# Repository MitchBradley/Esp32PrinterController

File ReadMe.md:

# ESP32 3D Printer Controller

This is based on https://github.com/felixstorm/Creality_Ender_3_ESP32_Board.git with the following changes

- Laid out for 2-sided PCB fabrication instead of PCB routing.  2-sided PCBs are available at very low cost from various prototyping shops, and provide much better grounding and power distribution.
- Can use either Pololu stepper driver modules or external drivers, selected by solder jumpers.
- The microstepping ratio can be selected by solder jumpers, or those pins can be connected to SPI for fine-grained configuration of TMC modules.  The X Y and Z axes all use the same microstepping/SPI settings, whereas the extruder can be configured independently of X, Y, Z.
- The I/O voltage to the shift registers and stepper modules can be either 3V3 or 5V, selected by solder jumper.  3V3 is appropriate for TMC modules where the SPI output goes back to the ESP32.  5V is best for external drivers whose optocoupler inputs work best at 5V.  Non-TMC stepper modules can use either.
- The micro SD card socket uses a Wemos D1 Mini shield which has a smaller footprint than the one on the original design, permitting all the drivers to be placed along one edge of the board.
- The connectors along the bottom edge of the board, and the power input connector, are all pluggable terminal blocks, thus permitting easy disconnection of the signals for assembly and maintenance.  The layout permits each signal pair to be on its own plug, or everything on one longer plug, or any combination thereof, at the users discretion.
- For the steppers, you can choose either 0.1" pitch connectors - e.g. pin headers with Dupont connectors - or 0.15" pitch pluggable terminal blocks (or 0.15" screw terminals, but pluggable is easier to wire and maintain).
- The fuse holders were spread out to make it easier to get your fingers in to grab the fuses.

The design passes acceptance checks for the aisler.net entry level prototyping service.

Update: The board is fully functional.  If you would like to build it, contact me and I will upload the revised version that fixes a few silkscreen errors and provides better clearance between some components that were a little crowded.

*Yet another Update:  Do not use the fan outputs; they are broken.  If you connect a fan it is likely to blow up the ULN2803A chip.  The problem - which I inherited from the base design and neglected to check - is that you cannot put ULN2803A channels in parallel and get them to share current.  ULN2803A use bipolar junction transistors - BJTs.  BJTs have a positive temperature coefficient, which means that, as the temperature increases, the collector current also increases.  When you put them in parallel, if one of them starts drawing a little more current than its neighbor, it gets hotter, and starts drawing even more current.  This is called "thermal runaway". Instead of sharing the load, one will take it all, then overheat and blow out, then the neighbor will take all the current and blow out, etc.  It is possible to make current-sharing circuits with BJTs, but ULN2803A does not have that kind of circuit.  The solution to the problem is to replace the ULN2803A with MOSFETs like that one that controls the extruder temperature.*

The board works with Marlin 2.0 for printer applications and with [Grbl_ESP32](https://github.com/bdring/Grbl_Esp32) for general CNC.

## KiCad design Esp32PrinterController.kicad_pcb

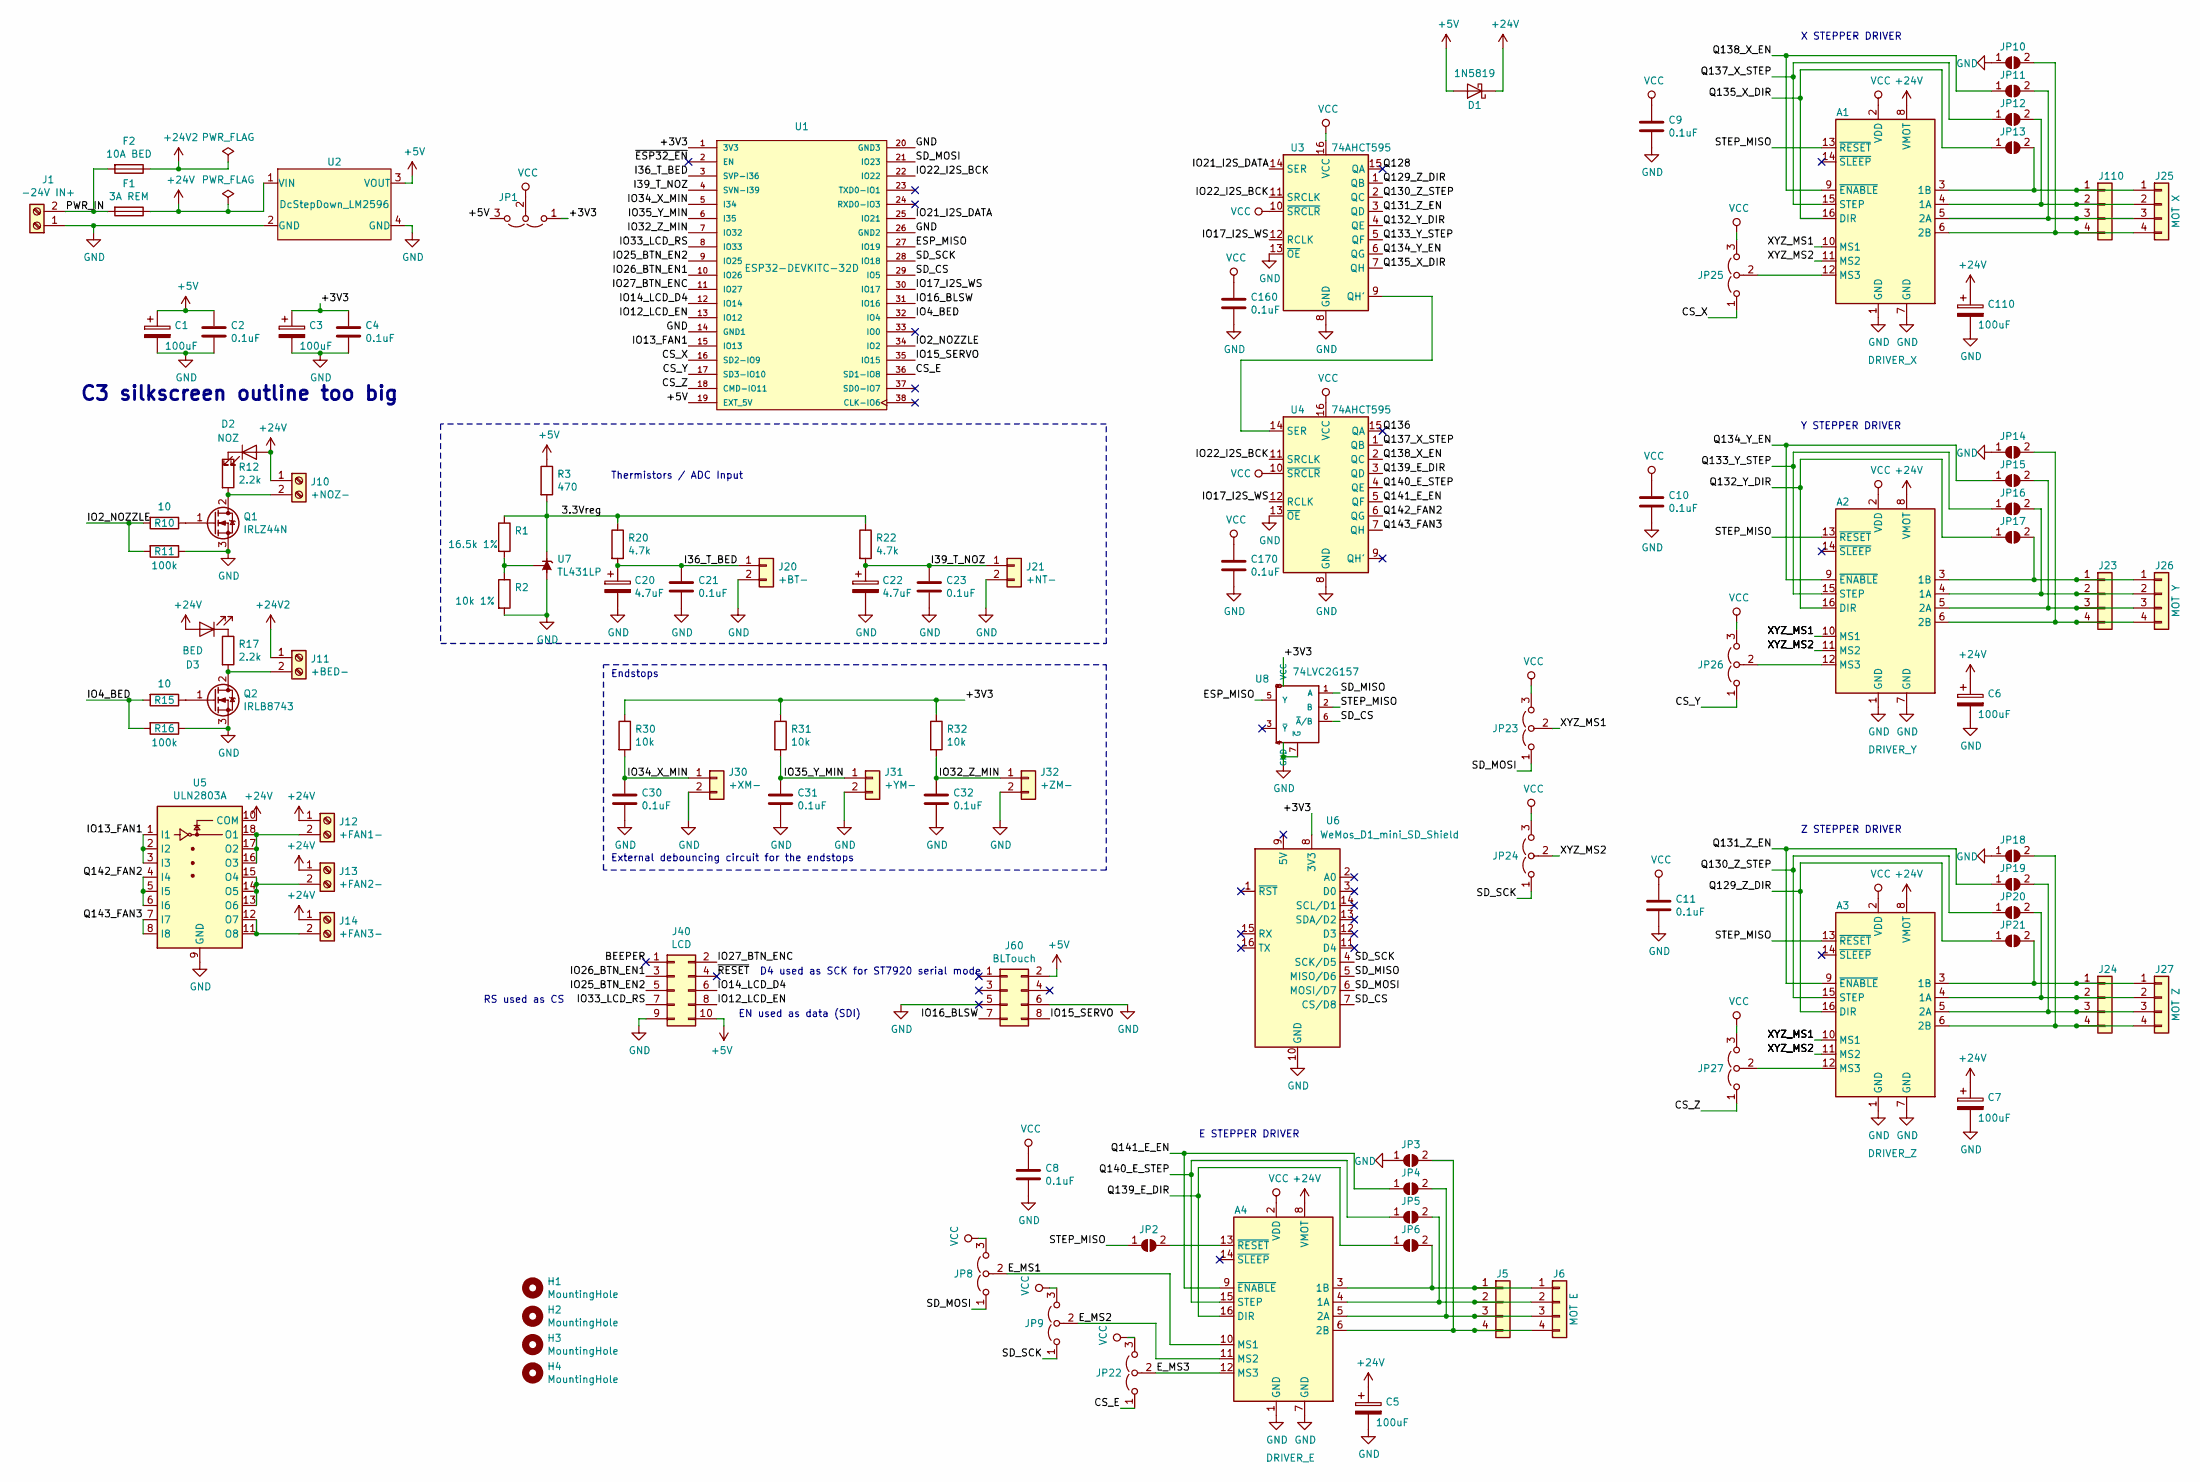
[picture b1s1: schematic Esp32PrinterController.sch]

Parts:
A1: DRIVER_X; Pololu_Breakout-16_15.2x20.3mm
A2: DRIVER_Y; Pololu_Breakout-16_15.2x20.3mm
A3: DRIVER_Z; Pololu_Breakout-16_15.2x20.3mm
A4: DRIVER_E; Pololu_Breakout-16_15.2x20.3mm
C1, C5, C6, C7, C110: 100uF; CP_Radial_D6.3mm_P2.50mm
C2, C4, C8, C9, C10, C11, C21, C23, C30, C31, C32, C160, C170: 0.1uF; C_Rect_L7.2mm_W2.5mm_P5.00mm_FKS2_FKP2_MKS2_MKP2
C3: 100uF; CP_Radial_D7.5mm_P2.50mm
C20, C22: 4.7uF; CP_Radial_D5.0mm_P2.00mm
D1: 1N5819; D_DO-35_SOD27_P10.16mm_Horizontal
D2: NOZ; LED_D5.0mm
D3: BED; LED_D5.0mm
F1: 3A REM; Fuseholder_Blade_ATO_Littelfuse_Pudenz_2_Pin
F2: 10A BED; Fuseholder_Blade_ATO_Littelfuse_Pudenz_2_Pin
H1, H2, H3, H4: MountingHole; MountingHole_3mm
J1: -24V IN+; PhoenixContact_MSTBVA_2,5_2-G-5,08_1x02_P5.08mm_Vertical
J5: MOT E; PinHeader_1x04_P2.54mm_Vertical
J6: MOT E; PhoenixContact_MCV_1,5_4-G-3.81_1x04_P3.81mm_Vertical
J10: +NOZ-; PhoenixContact_MSTBVA_2,5_2-G-5,08_1x02_P5.08mm_Vertical
J11: +BED-; PhoenixContact_MSTBVA_2,5_2-G-5,08_1x02_P5.08mm_Vertical
J12: +FAN1-; PhoenixContact_MSTBVA_2,5_2-G-5,08_1x02_P5.08mm_Vertical
J13: +FAN2-; PhoenixContact_MSTBVA_2,5_2-G-5,08_1x02_P5.08mm_Vertical
J14: +FAN3-; PhoenixContact_MSTBVA_2,5_2-G-5,08_1x02_P5.08mm_Vertical
J20: +BT-; PhoenixContact_MSTBVA_2,5_2-G-5,08_1x02_P5.08mm_Vertical
J21: +NT-; PhoenixContact_MSTBVA_2,5_2-G-5,08_1x02_P5.08mm_Vertical
J23: MOT Y; PinHeader_1x04_P2.54mm_Vertical
J24: MOT Z; PinHeader_1x04_P2.54mm_Vertical
J25: MOT X; PhoenixContact_MCV_1,5_4-G-3.81_1x04_P3.81mm_Vertical
J26: MOT Y; PhoenixContact_MCV_1,5_4-G-3.81_1x04_P3.81mm_Vertical
J27: MOT Z; PhoenixContact_MCV_1,5_4-G-3.81_1x04_P3.81mm_Vertical
J30: +XM-; PhoenixContact_MSTBVA_2,5_2-G-5,08_1x02_P5.08mm_Vertical
J31: +YM-; PhoenixContact_MSTBVA_2,5_2-G-5,08_1x02_P5.08mm_Vertical
J32: +ZM-; PhoenixContact_MSTBVA_2,5_2-G-5,08_1x02_P5.08mm_Vertical
J40: LCD; PinHeader_2x05_P2.54mm_Vertical
J60: BLTouch; PinHeader_2x04_P2.54mm_Vertical
J110: MOT X; PinHeader_1x04_P2.54mm_Vertical
JP1, JP8, JP9, JP22, JP23, JP24, JP25, JP26, JP27: Jumper_3_Open; SolderJumper-3_P1.3mm_Open_RoundedPad1.0x1.5mm_NumberLabels
JP2, JP3, JP4, JP5, JP6, JP10, JP11, JP12, JP13, JP14, JP15, JP16, JP17, JP18, JP19, JP20, JP21: SolderJumper_2_Open; SolderJumper-2_P1.3mm_Open_TrianglePad1.0x1.5mm
Q1: IRLZ44N; TO-220-3_Vertical
Q2: IRLB8743; TO-220-3_Vertical
R1: 16.5k 1%; R_Axial_DIN0207_L6.3mm_D2.5mm_P10.16mm_Horizontal
R2: 10k 1%; R_Axial_DIN0207_L6.3mm_D2.5mm_P10.16mm_Horizontal
R3: 470; R_Axial_DIN0207_L6.3mm_D2.5mm_P10.16mm_Horizontal
R10, R15: 10; R_Axial_DIN0207_L6.3mm_D2.5mm_P10.16mm_Horizontal
R11, R16: 100k; R_Axial_DIN0207_L6.3mm_D2.5mm_P10.16mm_Horizontal
R12, R17: 2.2k; R_Axial_DIN0207_L6.3mm_D2.5mm_P10.16mm_Horizontal
R20, R22: 4.7k; R_Axial_DIN0207_L6.3mm_D2.5mm_P10.16mm_Horizontal
R30, R31, R32: 10k; R_Axial_DIN0207_L6.3mm_D2.5mm_P10.16mm_Horizontal
U1: ESP32-DEVKITC-32D; MODULE_ESP32-DEVKITC-32D_LongPads
U2: DcStepDown_LM2596; Module_LM2596_DC-DC
U3, U4: 74AHCT595; DIP-16_W7.62mm_Socket_LongPads
U5: ULN2803A; DIP-18_W7.62mm_Socket_LongPads
U6: WeMos_D1_mini_SD_Shield; WEMOS_D1_mini_light
U7: TL431LP; TO-92_Inline
U8: 74LVC2G157; SSOP-8_2.95x2.8mm_P0.65mm

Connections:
+5V: C1.1, C2.1, D1.2 (A), J40.10, J60.2, JP1.3 (B), R3.1, U1.19 (EXT_5V), U2.3 (VOUT)
+24V: A1.8 (VMOT), A2.8 (VMOT), A3.8 (VMOT), A4.8 (VMOT), C5.1, C6.1, C7.1, C110.1, D1.1 (K), D2.2 (A), D3.2 (A), F1.1, J10.1, J12.1, J13.1, J14.1, U2.1 (VIN), U5.10 (COM)
+24V2: F2.1, J11.1
/3.3Vreg: R1.1, R3.2, R20.1, R22.1, U7.3 (K)
/+3V3: C3.1, C4.1, JP1.1 (A), R30.1, R31.1, R32.1, U1.1 (3V3), U6.8 (3V3), U8.8 (VCC)
/BEEPER: J40.1
/CS_E: JP22.1 (A), U1.36 (SD1-IO8)
/CS_X: JP25.1 (A), U1.16 (SD2-IO9)
/CS_Y: JP26.1 (A), U1.17 (SD3-IO10)
/CS_Z: JP27.1 (A), U1.18 (CMD-IO11)
/ESP_MISO: U1.27 (IO19), U8.5 (Y)
/E_MS1: A4.10 (MS1), JP8.2 (C)
/E_MS2: A4.11 (MS2), JP9.2 (C)
/E_MS3: A4.12 (MS3), JP22.2 (C)
/I36_T_BED: C20.1, C21.1, J20.1, R20.2, U1.3 (SVP-I36)
/I39_T_NOZ: C22.1, C23.1, J21.1, R22.2, U1.4 (SVN-I39)
/IO2_NOZZLE: R10.2, R11.2, U1.34 (IO2)
/IO4_BED: R15.2, R16.2, U1.32 (IO4)
/IO12_LCD_EN: J40.8, U1.13 (IO12)
/IO13_FAN1: U1.15 (IO13), U5.1 (I1), U5.2 (I2), U5.3 (I3)
/IO14_LCD_D4: J40.6, U1.12 (IO14)
/IO15_SERVO: J60.8, U1.35 (IO15)
/IO16_BLSW: J60.7, U1.31 (IO16)
/IO17_I2S_WS: U1.30 (IO17), U3.12 (RCLK), U4.12 (RCLK)
/IO21_I2S_DATA: U1.25 (IO21), U3.14 (SER)
/IO22_I2S_BCK: U1.22 (IO22), U3.11 (SRCLK), U4.11 (SRCLK)
/IO25_BTN_EN2: J40.5, U1.9 (IO25)
/IO26_BTN_EN1: J40.3, U1.10 (IO26)
/IO27_BTN_ENC: J40.2, U1.11 (IO27)
/IO32_Z_MIN: C32.1, J32.1, R32.2, U1.7 (IO32)
/IO33_LCD_RS: J40.7, U1.8 (IO33)
/IO34_X_MIN: C30.1, J30.1, R30.2, U1.5 (I34)
/IO35_Y_MIN: C31.1, J31.1, R31.2, U1.6 (I35)
/PWR_IN: F1.2, F2.2, J1.2
/Q128: U3.15 (QA)
/Q129_Z_DIR: A3.16 (DIR), JP21.1 (A), U3.1 (QB)
/Q130_Z_STEP: A3.15 (STEP), JP20.1 (A), U3.2 (QC)
/Q131_Z_EN: A3.9 (~ENABLE), JP19.1 (A), U3.3 (QD)
/Q132_Y_DIR: A2.16 (DIR), JP17.1 (A), U3.4 (QE)
/Q133_Y_STEP: A2.15 (STEP), JP16.1 (A), U3.5 (QF)
/Q134_Y_EN: A2.9 (~ENABLE), JP15.1 (A), U3.6 (QG)
/Q135_X_DIR: A1.16 (DIR), JP13.1 (A), U3.7 (QH)
/Q136: U4.15 (QA)
/Q137_X_STEP: A1.15 (STEP), JP12.1 (A), U4.1 (QB)
/Q138_X_EN: A1.9 (~ENABLE), JP11.1 (A), U4.2 (QC)
/Q139_E_DIR: A4.16 (DIR), JP6.1 (A), U4.3 (QD)
/Q140_E_STEP: A4.15 (STEP), JP5.1 (A), U4.4 (QE)
/Q141_E_EN: A4.9 (~ENABLE), JP4.1 (A), U4.5 (QF)
/Q142_FAN2: U4.6 (QG), U5.4 (I4), U5.5 (I5), U5.6 (I6)
/Q143_FAN3: U4.7 (QH), U5.7 (I7), U5.8 (I8)
/SD_CS: U1.29 (IO5), U6.7 (CS/D8), U8.6 (~A~/B)
/SD_MISO: U6.5 (MISO/D6), U8.1 (A)
/SD_MOSI: JP8.1 (A), JP23.1 (A), U1.21 (IO23), U6.6 (MOSI/D7)
/SD_SCK: JP9.1 (A), JP24.1 (A), U1.28 (IO18), U6.4 (SCK/D5)
/STEP_MISO: A1.13 (~RESET), A2.13 (~RESET), A3.13 (~RESET), JP2.1 (A), U8.2 (B)
/XYZ_MS1: A1.10 (MS1), A2.10 (MS1), A3.10 (MS1), JP23.2 (C)
/XYZ_MS2: A1.11 (MS2), A2.11 (MS2), A3.11 (MS2), JP24.2 (C)
/~ESP32_EN: U1.2 (EN)
/~RESET: J40.4
GND: A1.1 (GND), A1.7 (GND), A2.1 (GND), A2.7 (GND), A3.1 (GND), A3.7 (GND), A4.1 (GND), A4.7 (GND), C1.2, C2.2, C3.2, C4.2, C5.2, C6.2, C7.2, C8.2, C9.2, C10.2, C11.2, C20.2, C21.2, C22.2, C23.2, C30.2, C31.2, C32.2, C110.2, C160.2, C170.2, J1.1, J20.2, J21.2, J30.2, J31.2, J32.2, J40.9, J60.5, J60.6, JP3.1 (A), JP10.1 (A), JP14.1 (A), JP18.1 (A), Q1.3 (S), Q2.3 (S), R2.2, R11.1, R16.1, U1.14 (GND1), U1.20 (GND3), U1.26 (GND2), U2.2 (GND), U2.4 (GND), U3.8 (GND), U3.13 (~OE), U4.8 (GND), U4.13 (~OE), U5.9 (GND), U6.10 (GND), U7.2 (A), U8.4 (GND), U8.7 (~G)
unnamed: A1.3 (1B), J25.1, J110.1, JP13.2 (B)
unnamed: A1.4 (1A), J25.2, J110.2, JP12.2 (B)
unnamed: A1.5 (2A), J25.3, J110.3, JP11.2 (B)
unnamed: A1.6 (2B), J25.4, J110.4, JP10.2 (B)
unnamed: A1.12 (MS3), JP25.2 (C)
unnamed: A2.3 (1B), J23.1, J26.1, JP17.2 (B)
unnamed: A2.4 (1A), J23.2, J26.2, JP16.2 (B)
unnamed: A2.5 (2A), J23.3, J26.3, JP15.2 (B)
unnamed: A2.6 (2B), J23.4, J26.4, JP14.2 (B)
unnamed: A2.12 (MS3), JP26.2 (C)
unnamed: A3.3 (1B), J24.1, J27.1, JP21.2 (B)
unnamed: A3.4 (1A), J24.2, J27.2, JP20.2 (B)
unnamed: A3.5 (2A), J24.3, J27.3, JP19.2 (B)
unnamed: A3.6 (2B), J24.4, J27.4, JP18.2 (B)
unnamed: A3.12 (MS3), JP27.2 (C)
unnamed: A4.3 (1B), J5.1, J6.1, JP6.2 (B)
unnamed: A4.4 (1A), J5.2, J6.2, JP5.2 (B)
unnamed: A4.5 (2A), J5.3, J6.3, JP4.2 (B)
unnamed: A4.6 (2B), J5.4, J6.4, JP3.2 (B)
unnamed: A4.13 (~RESET), JP2.2 (B)
unnamed: D2.1 (K), R12.1
unnamed: D3.1 (K), R17.1
unnamed: J10.2, Q1.2 (D), R12.2
unnamed: J11.2, Q2.2 (D), R17.2
unnamed: J12.2, U5.16 (O3), U5.17 (O2), U5.18 (O1)
unnamed: J13.2, U5.13 (O6), U5.14 (O5), U5.15 (O4)
unnamed: J14.2, U5.11 (O8), U5.12 (O7)
unnamed: Q1.1 (G), R10.1
unnamed: Q2.1 (G), R15.1
unnamed: R1.2, R2.1, U7.1 (REF)
unnamed: U3.9 (QH'), U4.14 (SER)
VCC: A1.2 (VDD), A2.2 (VDD), A3.2 (VDD), A4.2 (VDD), C8.1, C9.1, C10.1, C11.1, C160.1, C170.1, JP1.2 (C), JP8.3 (B), JP9.3 (B), JP22.3 (B), JP23.3 (B), JP24.3 (B), JP25.3 (B), JP26.3 (B), JP27.3 (B), U3.10 (~SRCLR), U3.16 (VCC), U4.10 (~SRCLR), U4.16 (VCC)

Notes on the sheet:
X STEPPER DRIVER
Thermistors / ADC Input
Endstops
External debouncing circuit for the endstops
Y STEPPER DRIVER
Z STEPPER DRIVER
E STEPPER DRIVER
C3 silkscreen outline too big
D4 used as SCK for ST7920 serial mode
EN used as data (SDI)
RS used as CS

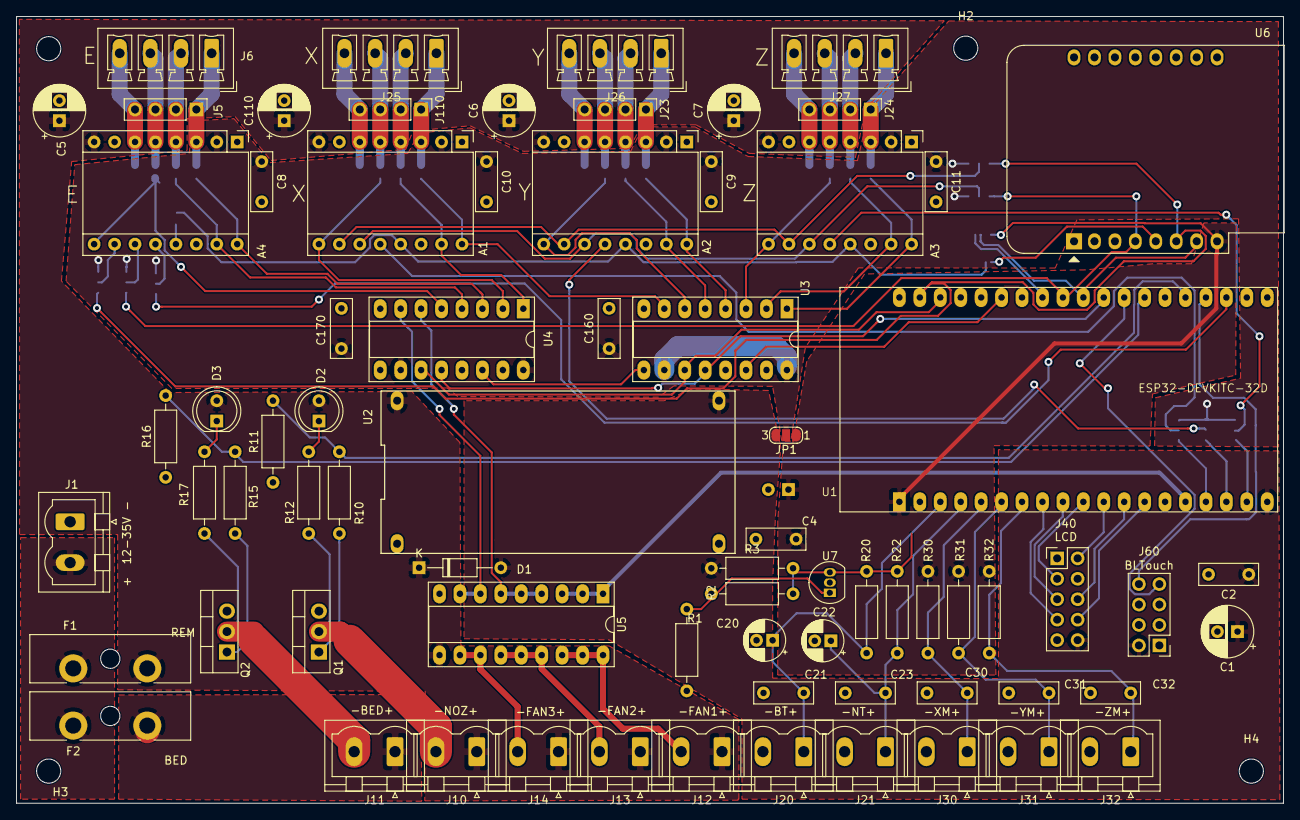
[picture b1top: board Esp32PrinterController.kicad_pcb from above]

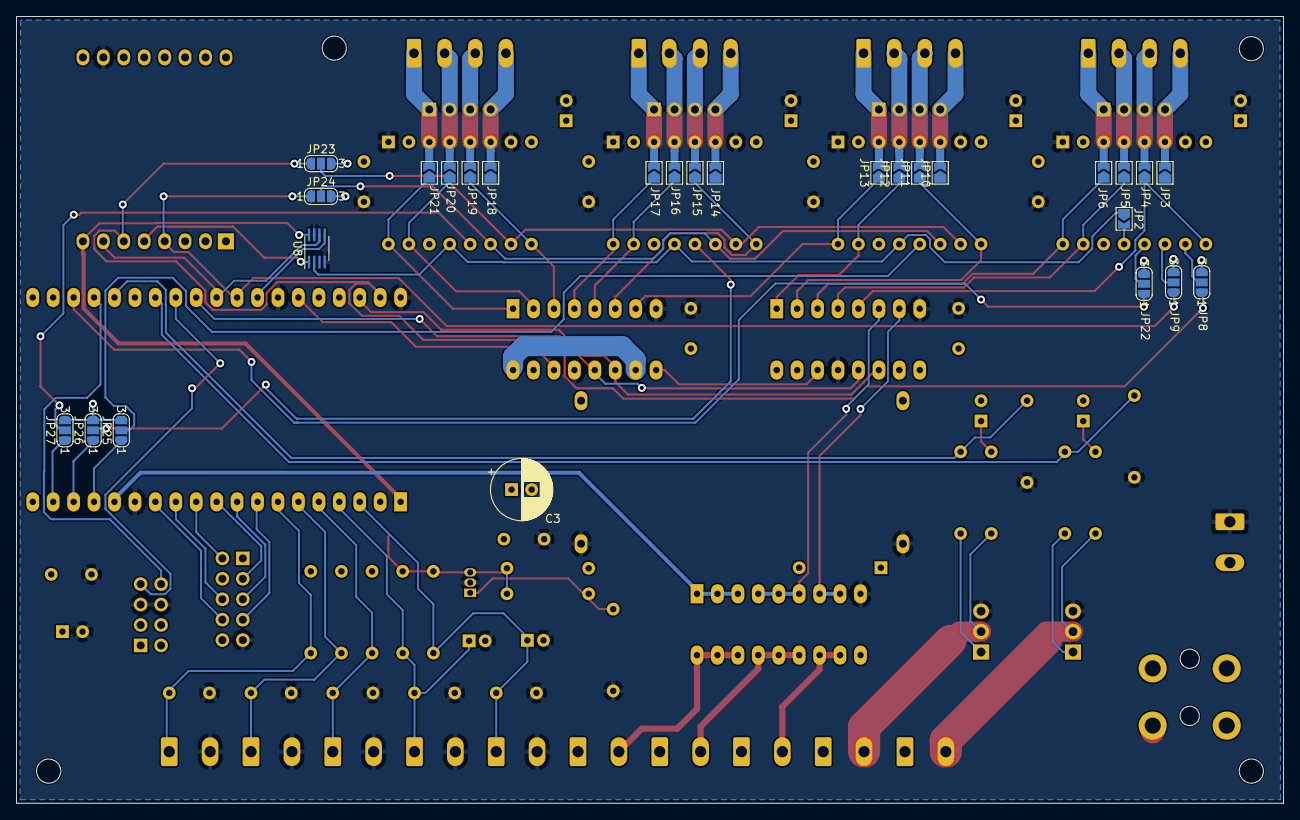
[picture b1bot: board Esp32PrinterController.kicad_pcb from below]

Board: 2 copper layers, 157.5 x 97.8 mm, 105 parts (27 on the bottom side), 87 nets.

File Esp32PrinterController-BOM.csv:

"Id";"Designator";"Package";"Quantity";"Designation";"Supplier and ref";
1;"J11";"PhoenixContact_MSTBVA_2,5_2-G-5,08_1x02_P5.08mm_Vertical_WallToWall";1;"+BED-";;;
2;"J1";"PhoenixContact_MSTBVA_2,5_2-G-5,08_1x02_P5.08mm_Vertical_WallToWall";1;"-24V IN+";;;
3;"J20";"PhoenixContact_MSTBVA_2,5_2-G-5,08_1x02_P5.08mm_Vertical_WallToWall";1;"+BT-";;;
4;"J21";"PhoenixContact_MSTBVA_2,5_2-G-5,08_1x02_P5.08mm_Vertical_WallToWall";1;"+NT-";;;
5;"J30";"PhoenixContact_MSTBVA_2,5_2-G-5,08_1x02_P5.08mm_Vertical_WallToWall";1;"+XM-";;;
6;"J31";"PhoenixContact_MSTBVA_2,5_2-G-5,08_1x02_P5.08mm_Vertical_WallToWall";1;"+YM-";;;
7;"J32";"PhoenixContact_MSTBVA_2,5_2-G-5,08_1x02_P5.08mm_Vertical_WallToWall";1;"+ZM-";;;
8;"J10";"PhoenixContact_MSTBVA_2,5_2-G-5,08_1x02_P5.08mm_Vertical_WallToWall";1;"+NOZ-";;;
9;"J12";"PhoenixContact_MSTBVA_2,5_2-G-5,08_1x02_P5.08mm_Vertical_WallToWall";1;"+FAN1-";;;
10;"J13";"PhoenixContact_MSTBVA_2,5_2-G-5,08_1x02_P5.08mm_Vertical_WallToWall";1;"+FAN2-";;;
11;"J14";"PhoenixContact_MSTBVA_2,5_2-G-5,08_1x02_P5.08mm_Vertical_WallToWall";1;"+FAN3-";;;
12;"U1";"MODULE_ESP32-DEVKITC-32D_LongPads";1;"ESP32-DEVKITC-32D";;;
13;"J60";"PinHeader_2x04_P2.54mm_Vertical";1;"BLTouch";;;
14;"J40";"PinHeader_2x05_P2.54mm_Vertical";1;"LCD";;;
15;"Q1";"TO-220-3_Vertical";1;"IRLZ44N";;;
16;"Q2";"TO-220-3_Vertical";1;"IRLB8743";;;
17;"JP15,JP2,JP3,JP4,JP5,JP6,JP7,JP10,JP11,JP12,JP13,JP14,JP16,JP17,JP18,JP19,JP20,JP21";"SolderJumper-2_P1.3mm_Open_TrianglePad1.0x1.5mm";18;"SolderJumper_2_Open";;;
18;"A2";"Pololu_Breakout-16_15.2x20.3mm";1;"DRIVER_Y";;;
19;"R16,R11";"R_Axial_DIN0207_L6.3mm_D2.5mm_P10.16mm_Horizontal";2;"100k";;;
20;"D2";"LED_D5.0mm";1;"NOZ";;;
21;"D3";"LED_D5.0mm";1;"BED";;;
22;"R17,R12";"R_Axial_DIN0207_L6.3mm_D2.5mm_P10.16mm_Horizontal";2;"2.2k";;;
23;"R15,R10";"R_Axial_DIN0207_L6.3mm_D2.5mm_P10.16mm_Horizontal";2;"10";;;
24;"C4,C2,C21,C23,C30,C160,C32,C170,C31,C8,C9,C10,C11";"C_Rect_L7.2mm_W2.5mm_P5.00mm_FKS2_FKP2_MKS2_MKP2";13;"0.1uF";;;
25;"R22,R20";"R_Axial_DIN0207_L6.3mm_D2.5mm_P10.16mm_Horizontal";2;"4.7k";;;
26;"H3,H4,H1,H2";"MountingHole_3mm";4;"MountingHole";;;
27;"D1";"D_DO-35_SOD27_P10.16mm_Horizontal";1;"1N5819";;;
28;"U2";"Module_LM2596_DC-DC";1;"DcStepDown_LM2596";;;
29;"R30,R31,R32";"R_Axial_DIN0207_L6.3mm_D2.5mm_P10.16mm_Horizontal";3;"10k";;;
30;"J6";"PhoenixContact_MCV_1,5_4-G-3.81_1x04_P3.81mm_Vertical";1;"MOT E";;;
31;"J25";"PhoenixContact_MCV_1,5_4-G-3.81_1x04_P3.81mm_Vertical";1;"MOT X";;;
32;"J26";"PhoenixContact_MCV_1,5_4-G-3.81_1x04_P3.81mm_Vertical";1;"MOT Y";;;
33;"J27";"PhoenixContact_MCV_1,5_4-G-3.81_1x04_P3.81mm_Vertical";1;"MOT Z";;;
34;"JP1";"SolderJumper-3_P2.0mm_Open_TrianglePad1.0x1.5mm_NumberLabels";1;"Jumper_3_Open";;;
35;"U6";"WEMOS_D1_mini_light";1;"WeMos_D1_mini_SD_Shield";;;
36;"JP8,JP9,JP22,JP23,JP24,JP25,JP26,JP27";"SolderJumper-3_P1.3mm_Open_RoundedPad1.0x1.5mm_NumberLabels";8;"Jumper_3_Open";;;
37;"J5";"PinHeader_1x04_P2.54mm_Vertical";1;"MOT E";;;
38;"J23";"PinHeader_1x04_P2.54mm_Vertical";1;"MOT Y";;;
39;"J24";"PinHeader_1x04_P2.54mm_Vertical";1;"MOT Z";;;
40;"A3";"Pololu_Breakout-16_15.2x20.3mm";1;"DRIVER_Z";;;
41;"A4";"Pololu_Breakout-16_15.2x20.3mm";1;"DRIVER_E";;;
42;"C5,C6,C7,C110,C1";"CP_Radial_D6.3mm_P2.50mm";5;"100uF";;;
43;"C22,C20";"CP_Radial_D5.0mm_P2.00mm";2;"4.7uF";;;
44;"A1";"Pololu_Breakout-16_15.2x20.3mm";1;"DRIVER_X";;;
45;"C3";"CP_Radial_D7.5mm_P2.50mm";1;"100uF";;;
46;"F1";"Fuseholder_Blade_ATO_Littelfuse_Pudenz_2_Pin";1;"3A REM";;;
47;"F2";"Fuseholder_Blade_ATO_Littelfuse_Pudenz_2_Pin";1;"10A BED";;;
48;"J110";"PinHeader_1x04_P2.54mm_Vertical";1;"MOT X";;;
49;"U3,U4";"DIP-16_W7.62mm_Socket_LongPads";2;"74AHCT595";;;
50;"U5";"DIP-18_W7.62mm_Socket_LongPads";1;"ULN2803A";;;

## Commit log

2020-02-28 Initial revision
2020-03-19 Added notes for next rev
2020-03-20 Layout for D1 Mini form factor
2020-04-23 Added update at end
2020-05-12 Added photo and Grbl_ESP32 reference.
2020-06-16 Warn about fan bug
2021-10-03 Rev2, unbuilt
